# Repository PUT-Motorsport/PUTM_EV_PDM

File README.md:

# PUTM_EV_PDM
kopia src-brak całego projektu w tym branchu

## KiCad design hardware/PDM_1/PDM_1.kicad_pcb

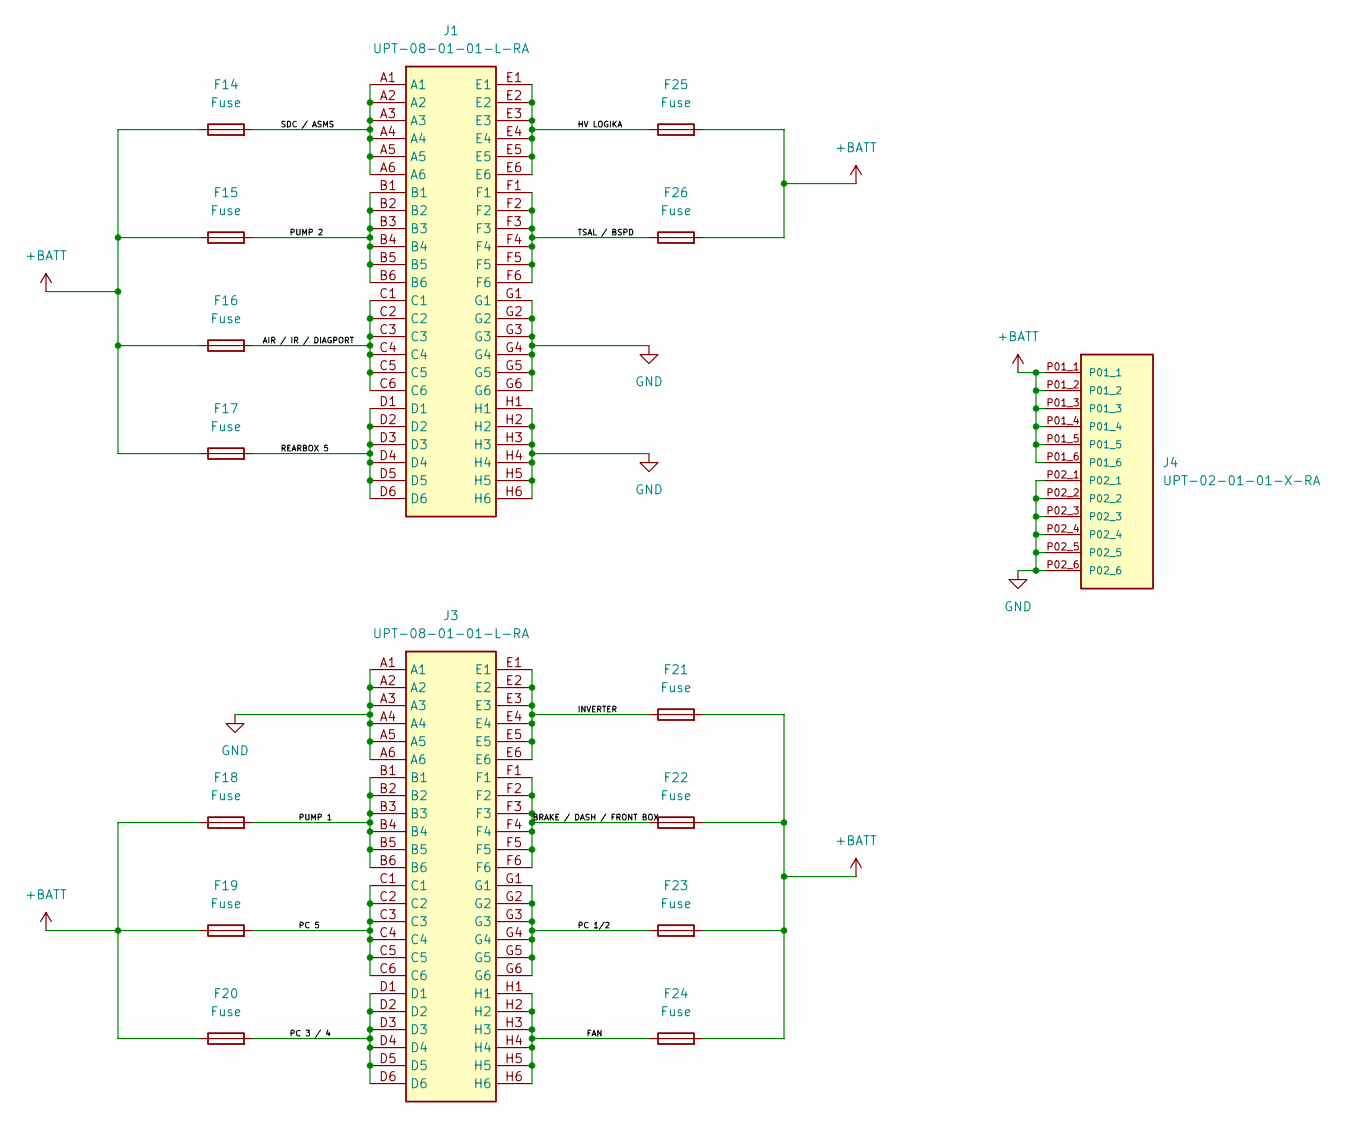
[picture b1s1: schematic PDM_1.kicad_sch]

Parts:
F14, F15, F16, F17, F18, F19, F20, F21, F22, F23, F24, F25, F26: Fuse; 3568
J1, J3: UPT-08-01-01-L-RA; UPT080101LRA; Mouser Part Number 200-UPT080101LRA
J4: UPT-02-01-01-X-RA; SAMTEC_UPT-02-01-01-X-RA; PARTREV C

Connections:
+BATT: F14.1, F15.1, F16.1, F17.1, F18.1, F19.1, F20.1, F21.2, F22.2, F23.2, F24.2, F25.2, F26.2, J4.P01_1, J4.P01_2, J4.P01_3, J4.P01_4, J4.P01_5, J4.P01_6
/AIR / IR / DIAGPORT: F16.2, J1.C1, J1.C2, J1.C3, J1.C4, J1.C5, J1.C6
/BRAKE / DASH / FRONT BOX: F22.1, J3.F1, J3.F2, J3.F3, J3.F4, J3.F5, J3.F6
/FAN: F24.1, J3.H1, J3.H2, J3.H3, J3.H4, J3.H5, J3.H6
/HV LOGIKA: F25.1, J1.E1, J1.E2, J1.E3, J1.E4, J1.E5, J1.E6
/INVERTER: F21.1, J3.E1, J3.E2, J3.E3, J3.E4, J3.E5, J3.E6
/PC 1/2: F23.1, J3.G1, J3.G2, J3.G3, J3.G4, J3.G5, J3.G6
/PC 3 / 4: F20.2, J3.D1, J3.D2, J3.D3, J3.D4, J3.D5, J3.D6
/PC 5: F19.2, J3.C1, J3.C2, J3.C3, J3.C4, J3.C5, J3.C6
/PUMP 1: F18.2, J3.B1, J3.B2, J3.B3, J3.B4, J3.B5, J3.B6
/PUMP 2: F15.2, J1.B1, J1.B2, J1.B3, J1.B4, J1.B5, J1.B6
/REARBOX 5: F17.2, J1.D1, J1.D2, J1.D3, J1.D4, J1.D5, J1.D6
/SDC / ASMS: F14.2, J1.A1, J1.A2, J1.A3, J1.A4, J1.A5, J1.A6
/TSAL / BSPD: F26.1, J1.F1, J1.F2, J1.F3, J1.F4, J1.F5, J1.F6
GND: J1.G1, J1.G2, J1.G3, J1.G4, J1.G5, J1.G6, J1.H1, J1.H2, J1.H3, J1.H4, J1.H5, J1.H6, J3.A1, J3.A2, J3.A3, J3.A4, J3.A5, J3.A6, J4.P02_1, J4.P02_2, J4.P02_3, J4.P02_4, J4.P02_5, J4.P02_6

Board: 4 copper layers, 16 parts (0 on the bottom side), 15 nets, no tracks yet.

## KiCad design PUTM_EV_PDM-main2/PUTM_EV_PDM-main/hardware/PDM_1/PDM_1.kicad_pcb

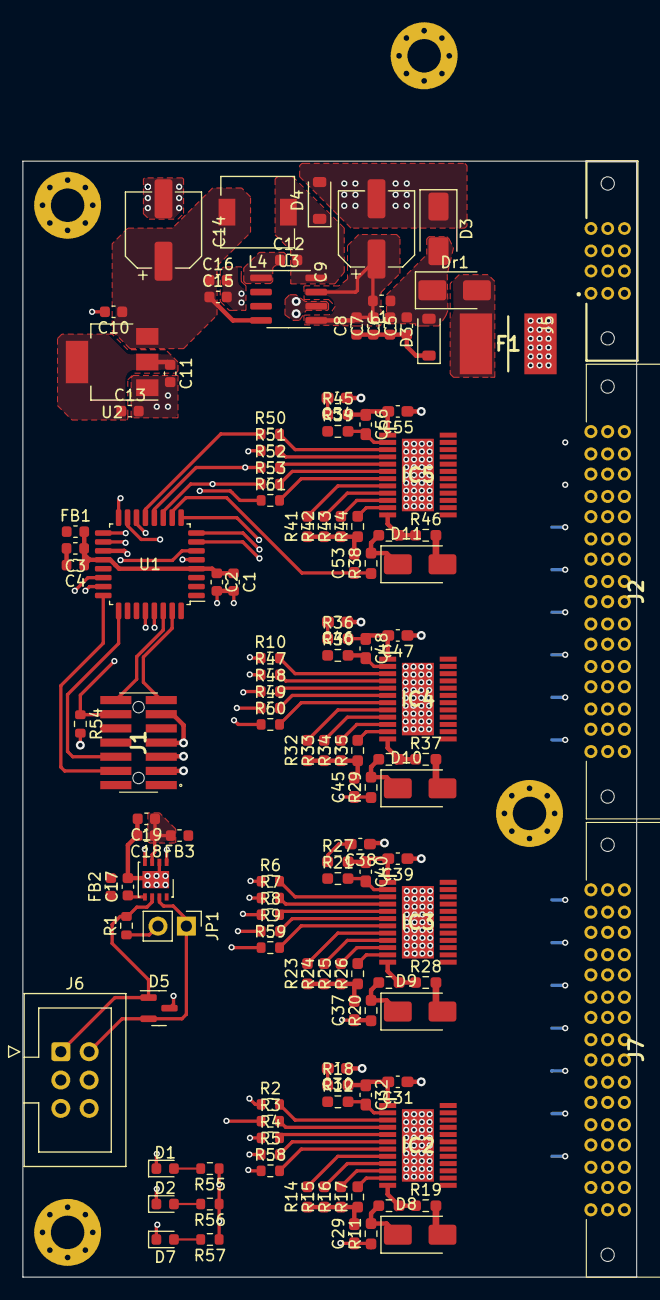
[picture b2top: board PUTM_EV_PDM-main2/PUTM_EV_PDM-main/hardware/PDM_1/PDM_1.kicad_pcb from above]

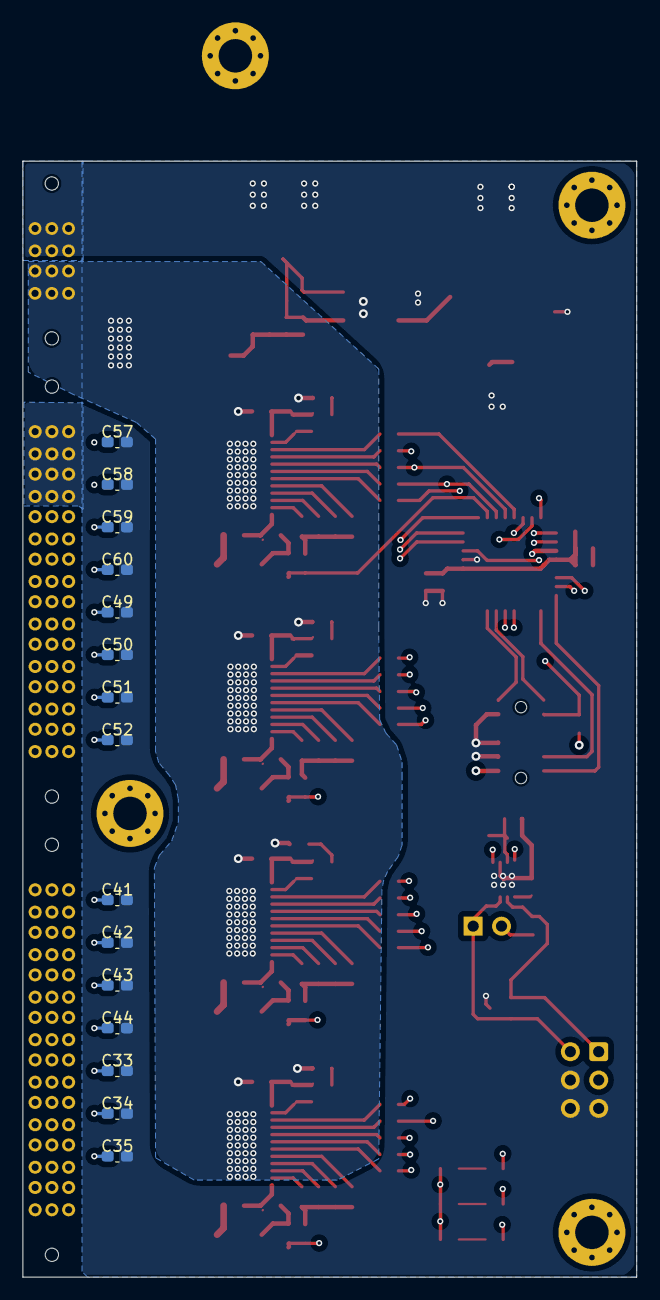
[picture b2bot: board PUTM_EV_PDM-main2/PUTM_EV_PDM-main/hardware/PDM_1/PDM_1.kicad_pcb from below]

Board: 4 copper layers, 55.0 x 100.0 mm, 143 parts (15 on the bottom side), 111 nets.

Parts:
C1, C3: 100n; L_0603_1608Metric
C2, C4: 4.7u; L_0603_1608Metric
C5, C11, C15: 1u; C_0603_1608Metric
C6: 10u; C_0603_1608Metric
C7, C8, C10, C13, C16, C17, C19: 100n; C_0603_1608Metric
C9: 100u; CP_Elec_6.3x7.7
C12: 10n; C_0603_1608Metric
C14: 68u; CP_Elec_6.3x5.4
C18: 10uF; C_0603_1608Metric
C29, C37, C45, C53: 220p; C_0603_1608Metric_Pad1.08x0.95mm_HandSolder
C30, C38, C46, C54: 100n; C_0603_1608Metric_Pad1.08x0.95mm_HandSolder
C31, C39, C47, C55: 22n; C_0603_1608Metric_Pad1.08x0.95mm_HandSolder
C32, C40, C48, C56: 470n; C_0603_1608Metric_Pad1.08x0.95mm_HandSolder
C33, C34, C35, C41, C42, C43, C44, C49, C50, C51, C52, C57, C58, C59, C60: 10n; C_0603_1608Metric_Pad1.08x0.95mm_HandSolder
D1, D2, D7: LED; LED_0603_1608Metric
D3: PESD24VF1BLYL; D_SMA
D3#2, D4: D_Schottky_Small; D_SOD-123
D5: PESD2CAN.215; SOT-23
D8, D9, D10, D11: D_Schottky; D_SMA
Dr1: SS34ALH; D_SMA
F1: 2920L050_72DR; FUSC7451X125N
FB1: FerriteBead_Small; L_0603_1608Metric
FB2, FB3: 60R@100MHz; L_0603_1608Metric
IC2, IC3, IC4, IC5: BTS722204ESAXUMA1; SOP65P600X115-25N
J1: FTSH-107-01-L-DV-K-A; FTSH-107-XX-YYY-DV-K-A
J2, J7: UPT-08-01-01-L-RA; UPT080101LRA
J5: UPT-02-01-01-X-RA; SAMTEC_UPT-02-01-01-X-RA
J6: Conn_01x06; IDC-Header_2x03_P2.54mm_Vertical
JP1: Jumper_2_Bridged; PinHeader_1x02_P2.54mm_Vertical
L1: 300n; L_0603_1608Metric
L4: 47u; L_6.3x6.3_H3
R1: 120; R_0603_1608Metric
R2, R3, R4, R5, R6, R7, R8, R9, R10, R47, R48, R49, R50, R51, R52, R53: 1.2k; R_0603_1608Metric
R11, R13, R20, R22, R29, R31, R38, R40: 4.7k; R_0603_1608Metric_Pad0.98x0.95mm_HandSolder
R12, R21, R30, R39: 470; R_0603_1608Metric_Pad0.98x0.95mm_HandSolder
R14, R15, R16, R17, R23, R24, R25, R26, R32, R33, R34, R35, R41, R42, R43, R44: 10k; R_0603_1608Metric_Pad0.98x0.95mm_HandSolder
R18, R27, R36, R45: 47; R_0603_1608Metric_Pad0.98x0.95mm_HandSolder
R19, R28, R37, R46: 1.2k; R_0603_1608Metric_Pad0.98x0.95mm_HandSolder
R54: 100k; R_0603_1608Metric
R55, R56, R57: 330; R_0603_1608Metric
R58, R59, R60, R61: 4.7k; R_0603_1608Metric
U1: STM32G0C1KCTxN; LQFP-32_7x7mm_P0.8mm
U2: LD1117S33TR_SOT223; SOT-223-3_TabPin2
U3: LM2675M-5.0/NOPB; SOIC-8_3.9x4.9mm_P1.27mm
U5: MCP2542FDxMF; DFN-8-1EP_3x3mm_P0.65mm_EP1.55x2.4mm

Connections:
+3.3V: C11.1, C13.1, FB1.1, FB2.2, J1.3, R12.1, R21.1, R30.1, R39.1, R54.2, R55.1, R56.1, R57.1, U2.2 (VO)
+5V: C10.1, C14.1, C15.1, C16.1, FB3.1, L4.2, U2.3 (VI), U3.4 (FB)
+BATT: C30.1, C31.1, C38.1, C39.1, C46.1, C47.1, C54.1, C55.1, F1.2, IC2.25 (VS), IC3.25 (VS), IC4.25 (VS), IC5.25 (VS), J5.P01_1, J5.P01_2, J5.P01_3, J5.P01_4, J5.P01_5, J5.P01_6
/CAN/CAN_VDD: C18.1, C19.1, FB3.2, U5.3 (VDD)
/CAN_RXD: U1.22 (PA11/PA9), U5.4 (RXD)
/CAN_TXD: U1.23 (PA12/PA10), U5.1 (TXD)
/FUSE1_IS: C29.1, R11.1, U1.7 (PA0)
/FUSE2_IS: C37.1, R20.1, U1.8 (PA1)
/FUSE3_IS: C45.1, R29.1, U1.9 (PA2)
/FUSE4_IS: C53.1, R38.1, U1.10 (PA3)
/LED1: D1.1 (K), U1.19 (PA9/UCPD1_DBCC1)
/LED2: D2.1 (K), U1.18 (PA8)
/LED3: D7.1 (K), U1.17 (PB15)
/LHI_1: R58.1, U1.28 (PD2)
/LHI_2: R59.1, U1.29 (PD3)
/LHI_3: R60.1, U1.15 (PB0)
/LHI_4: R61.1, U1.16 (PB1)
/NRST: J1.12, R54.1, U1.6 (PF2)
/SPI1_MISO: R50.1, U1.13 (PA6)
/SPI1_MOSI: R3.1, U1.14 (PA7)
/SPI1_NSS: R5.1, R9.1, R49.1, R53.1, U1.11 (PA4)
/SPI1_SCK: R4.1, R8.1, R48.1, R52.1, U1.12 (PA5)
/STM_VCC: C1.1, C2.1, C3.1, C4.1, FB1.2, U1.4 (VDD), U1.20 (VDDIO2)
/SWCLK: J1.6, U1.25 (PA14)
/SWDIO: J1.4, U1.24 (PA13)
/USART1_RX: J1.13, U1.31 (PB7)
/USART1_TX: J1.14, U1.30 (PB6)
/battery connection/IC_1/IN0: IC2.8 (IN0), R14.2
/battery connection/IC_1/IN1: IC2.9 (IN1), R15.2
/battery connection/IC_1/IN2: IC2.10 (IN2), R16.2
/battery connection/IC_1/IN3: IC2.11 (IN3), R17.2
/battery connection/IC_2/IN0: IC3.8 (IN0), R23.2
/battery connection/IC_2/IN1: IC3.9 (IN1), R24.2
/battery connection/IC_2/IN2: IC3.10 (IN2), R25.2
/battery connection/IC_2/IN3: IC3.11 (IN3), R26.2
/battery connection/IC_3/IN0: IC4.8 (IN0), R32.2
/battery connection/IC_3/IN1: IC4.9 (IN1), R33.2
/battery connection/IC_3/IN2: IC4.10 (IN2), R34.2
/battery connection/IC_3/IN3: IC4.11 (IN3), R35.2
/battery connection/IC_4/IN0: IC5.8 (IN0), R41.2
/battery connection/IC_4/IN1: IC5.9 (IN1), R42.2
/battery connection/IC_4/IN2: IC5.10 (IN2), R43.2
/battery connection/IC_4/IN3: IC5.11 (IN3), R44.2
/battery connection/MISO_1: R2.1, R7.1
/battery connection/MISO_2: R6.1, R47.1
/battery connection/MISO_3: R10.1, R51.1
/power/CB: C12.1, U3.1 (CB)
/power/SW_L: C12.2, D4.1 (K), L4.1, U3.8 (VSW)
/power/VIN: Dr1.2 (A), F1.1
/power/VIN_L: C5.2, C6.2, D3.2 (A2), D3#2.2 (A), Dr1.1 (K), L1.1
/power/VIN_SW_REG: C7.2, C8.2, C9.1, L1.2, U3.5 (ON/~OFF), U3.7 (VIN)
CAN_H: D5.2 (A2), J6.2, JP1.1 (A), U5.7 (CANH)
CAN_L: D5.1 (A1), J6.1, R1.2, U5.6 (CANL)
GND: C1.2, C2.2, C3.2, C4.2, C5.1, C6.1, C7.1, C8.1, C9.2, C10.2, C11.2, C13.2, C14.2, C15.2, C16.2, C17.2, C18.2, C19.2, C29.2, C30.2, C33.2, C34.2, C35.2, C37.2, C38.2, C41.2, C42.2, C43.2, C44.2, C45.2, C46.2, C49.2, C50.2, C51.2, C52.2, C53.2, C54.2, C57.2, C58.2, C59.2, C60.2, D3.1 (A1), D3#2.1 (K), D4.2 (A), D5.3 (common), D8.2 (A), D9.2 (A), D10.2 (A), D11.2 (A), J1.5, J1.7, J1.11, J2.G1, J2.G2, J2.G3, J2.G4, J2.G5, J2.G6, J2.H1, J2.H2, J2.H3, J2.H4, J2.H5, J2.H6, J5.P02_1, J5.P02_2, J5.P02_3, J5.P02_4, J5.P02_5, J5.P02_6, J6.4, J6.5, J6.6, J7.A1, J7.A2, J7.A3, J7.A4, J7.A5, J7.A6, R14.1, R15.1, R16.1, R17.1, R18.1, R19.2, R23.1, R24.1, R25.1, R26.1, R27.1, R28.2, R32.1, R33.1, R34.1, R35.1, R36.1, R37.2, R41.1, R42.1, R43.1, R44.1, R45.1, R46.2, U1.5 (VSS), U2.1 (GND), U3.6 (GND), U5.2 (VSS), U5.8 (STBY), U5.9 (VSS)
unnamed: D1.2 (A), R55.2
unnamed: D2.2 (A), R56.2
unnamed: D7.2 (A), R57.2
unnamed: D8.1 (K), R11.2, R13.1
unnamed: D9.1 (K), R20.2, R22.1
unnamed: D10.1 (K), R29.2, R31.1
unnamed: D11.1 (K), R38.2, R40.1
unnamed: IC2.6 (CSN), R5.2
unnamed: C31.2, C32.1, IC2.1 (GND_1), R18.2
unnamed: IC2.12 (IS), R13.2, R19.1
unnamed: IC2.7 (LHI), R58.2
unnamed: IC2.5 (SCLK), R4.2
unnamed: IC2.4 (SI), R3.2
unnamed: IC2.3 (SO), R2.2
unnamed: C32.2, IC2.2 (VDD), R12.2
unnamed: IC3.6 (CSN), R9.2
unnamed: C39.2, C40.1, IC3.1 (GND_1), R27.2
unnamed: IC3.12 (IS), R22.2, R28.1
unnamed: IC3.7 (LHI), R59.2
unnamed: IC3.5 (SCLK), R8.2
unnamed: IC3.4 (SI), R7.2
unnamed: IC3.3 (SO), R6.2
unnamed: C40.2, IC3.2 (VDD), R21.2
unnamed: IC4.6 (CSN), R49.2
unnamed: C47.2, C48.1, IC4.1 (GND_1), R36.2
unnamed: IC4.12 (IS), R31.2, R37.1
unnamed: IC4.7 (LHI), R60.2
unnamed: IC4.5 (SCLK), R48.2
unnamed: IC4.4 (SI), R47.2
unnamed: IC4.3 (SO), R10.2
unnamed: C48.2, IC4.2 (VDD), R30.2
unnamed: IC5.6 (CSN), R53.2
unnamed: C55.2, C56.1, IC5.1 (GND_1), R45.2
unnamed: IC5.12 (IS), R40.2, R46.1
unnamed: IC5.7 (LHI), R61.2
unnamed: IC5.5 (SCLK), R52.2
unnamed: IC5.4 (SI), R51.2
unnamed: IC5.3 (SO), R50.2
unnamed: C56.2, IC5.2 (VDD), R39.2
unnamed: JP1.2 (B), R1.1
unnamed: C17.1, FB2.1, U5.5 (VIO)
OUT1_0: C33.1, IC2.21 (OUT0_1), IC2.22 (OUT0_2), IC2.23 (OUT0_3), IC2.24 (OUT0_4), J7.D1, J7.D2, J7.D3, J7.D4, J7.D5, J7.D6
OUT1_1: C34.1, IC2.19 (OUT1_1), IC2.20 (OUT1_2), J7.C1, J7.C2, J7.C3, J7.C4, J7.C5, J7.C6
OUT1_2: C35.1, IC2.17 (OUT2_1), IC2.18 (OUT2_2), J7.B1, J7.B2, J7.B3, J7.B4, J7.B5, J7.B6
OUT1_3: IC2.13 (OUT3_1), IC2.14 (OUT3_2), IC2.15 (OUT3_3), IC2.16 (OUT3_4)
OUT2_0: C41.1, IC3.21 (OUT0_1), IC3.22 (OUT0_2), IC3.23 (OUT0_3), IC3.24 (OUT0_4), J7.H1, J7.H2, J7.H3, J7.H4, J7.H5, J7.H6
OUT2_1: C42.1, IC3.19 (OUT1_1), IC3.20 (OUT1_2), J7.G1, J7.G2, J7.G3, J7.G4, J7.G5, J7.G6
OUT2_2: C43.1, IC3.17 (OUT2_1), IC3.18 (OUT2_2), J7.F1, J7.F2, J7.F3, J7.F4, J7.F5, J7.F6
OUT2_3: C44.1, IC3.13 (OUT3_1), IC3.14 (OUT3_2), IC3.15 (OUT3_3), IC3.16 (OUT3_4), J7.E1, J7.E2, J7.E3, J7.E4, J7.E5, J7.E6
OUT3_0: C49.1, IC4.21 (OUT0_1), IC4.22 (OUT0_2), IC4.23 (OUT0_3), IC4.24 (OUT0_4), J2.D1, J2.D2, J2.D3, J2.D4, J2.D5, J2.D6
OUT3_1: C50.1, IC4.19 (OUT1_1), IC4.20 (OUT1_2), J2.C1, J2.C2, J2.C3, J2.C4, J2.C5, J2.C6
OUT3_2: C51.1, IC4.17 (OUT2_1), IC4.18 (OUT2_2), J2.B1, J2.B2, J2.B3, J2.B4, J2.B5, J2.B6
OUT3_3: C52.1, IC4.13 (OUT3_1), IC4.14 (OUT3_2), IC4.15 (OUT3_3), IC4.16 (OUT3_4), J2.A1, J2.A2, J2.A3, J2.A4, J2.A5, J2.A6
OUT4_0: C57.1, IC5.21 (OUT0_1), IC5.22 (OUT0_2), IC5.23 (OUT0_3), IC5.24 (OUT0_4)
OUT4_1: C58.1, IC5.19 (OUT1_1), IC5.20 (OUT1_2)
OUT4_2: C59.1, IC5.17 (OUT2_1), IC5.18 (OUT2_2), J2.F1, J2.F2, J2.F3, J2.F4, J2.F5, J2.F6
OUT4_3: C60.1, IC5.13 (OUT3_1), IC5.14 (OUT3_2), IC5.15 (OUT3_3), IC5.16 (OUT3_4), J2.E1, J2.E2, J2.E3, J2.E4, J2.E5, J2.E6

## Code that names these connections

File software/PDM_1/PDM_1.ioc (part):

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Mcu.Name=STM32G0C1K(C-E)TxN
Mcu.Package=LQFP32
Mcu.UserName=STM32G0C1KCTxN
PA0.GPIOParameters=GPIO_Label
PA0.GPIO_Label=FUSE1_IS
PA0.Mode=IN0
PA0.Signal=ADC1_IN0
PA1.GPIOParameters=GPIO_Label
PA1.GPIO_Label=FUSE2_IS
PA1.Mode=IN1
PA1.Signal=ADC1_IN1
PA11\ [PA9].Mode=FDCAN_Activate
PA11\ [PA9].Signal=FDCAN1_RX
PA12\ [PA10].Mode=FDCAN_Activate
PA12\ [PA10].Signal=FDCAN1_TX
PA13.Mode=Serial_Wire
PA13.Signal=SYS_SWDIO
PA14-BOOT0.Mode=Serial_Wire
PA14-BOOT0.Signal=SYS_SWCLK
PA2.GPIOParameters=GPIO_Label
PA2.GPIO_Label=FUSE3_IS
PA2.Mode=IN2
PA2.Signal=ADC1_IN2
PA3.GPIOParameters=GPIO_Label
PA3.GPIO_Label=FUSE4_IS
PA3.Mode=IN3
PA3.Signal=ADC1_IN3
PA4.Signal=SPI1_NSS
PA5.Mode=Full_Duplex_Master
PA5.Signal=SPI1_SCK
PA6.Mode=Full_Duplex_Master
PA6.Signal=SPI1_MISO
PA7.Mode=Full_Duplex_Master
PA7.Signal=SPI1_MOSI
PA8.GPIOParameters=GPIO_Label
PA8.GPIO_Label=LED2
PA8.Signal=GPIO_Output
PA9.GPIOParameters=GPIO_Label
PA9.GPIO_Label=LED1
PA9.Signal=GPIO_Output
PB0.GPIOParameters=GPIO_Label
PB0.GPIO_Label=LHI_3
PB0.Signal=GPIO_Output
PB1.GPIOParameters=GPIO_Label
PB1.GPIO_Label=LHI_4
PB1.Signal=GPIO_Output
PB15.GPIOParameters=GPIO_Label
PB15.GPIO_Label=LED3
PB15.Signal=GPIO_Output
PB6.Signal=USART1_TX
PB7.Signal=USART1_RX
PD2.GPIOParameters=GPIO_Label
PD2.GPIO_Label=LHI_1
PD2.Signal=GPIO_Output
PD3.GPIOParameters=GPIO_Label
PD3.GPIO_Label=LHI_2
PD3.Signal=GPIO_Output
RCC.HSE_VALUE=8000000
RCC.SYSCLKFreq_VALUE=64000000
RCC.SYSCLKSource=RCC_SYSCLKSOURCE_PLLCLK
board=custom

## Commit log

2024-02-20 PDM1
2024-02-29 gitignore update
2024-02-29 firmware first update
2024-03-05 lepsze footprinty
2024-03-11 nowe połączenia
    dodane połączenia z STM
    dodane złącza
    dodane LED
2024-03-20 małe zmiany
    dodano złącza
    zmieniono parę footprintów
2024-03-27 piny na płytce
    Dodano ułożenie pinów na płytce
2024-03-27 Zamienione 2 i 8 pin
2024-04-07 Połączenia w grupach
2024-04-08 Nowe ułożenie na płytce
    Ułożenie komponentów na płytce
    Dodane połączenie +24V
2024-04-13 Koniec połączeń sygnałów
    Wszystkie sygnały z stm poprowadzone
    Zmienione ułożenie połączeń do złącz
2024-04-16 Nowe połączenia
    dodana warstwa gnd
2024-04-16 Porządki w folderze
2024-04-20 Do sprawdzenia
    Skończone połączenia
    Zrobione przelotki
2024-04-21 Poprawki
2024-04-21 Poprawki2
2024-04-21 Poprawki 3
2024-04-21 Poprawki 4
2024-04-21 Poprawki 5
2024-04-28 Poprawki6
2024-04-28 Koniec
2024-05-29 Initial commit for software
2024-06-06 Transfer from PDM to simple FuseBox
2024-06-06 Logo and description added
2024-06-07 to be continued :>
2024-06-10 working_outs
2024-06-10 measurement of several channels
2024-06-11 testy zamykania tran
2024-06-11 5A / 4A
2024-06-11 4A i 5 A pop
2024-06-18 BEZ 3
